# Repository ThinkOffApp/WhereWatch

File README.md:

# WhereWatch

**A pendant that remembers where you left things — fully local.** A tiny
wearable camera photo-logs your day into a Raspberry Pi at home; a local
vision model watches the trail. Ask *"where are my keys?"* and get back the
last photo that contains them, with a timestamp. No cloud, no subscription,
nothing leaves your house.

## Two devices. Zero cloud.

Plug in the Raspberry Pi. Charge the pendant over USB-C. Wear it.
That is the whole system. CodeWatch is the phone and watch dashboard for the same local *Watch family.

WhereWatch remembers where you placed your things, privately. The Pi stores
a photo of the last useful observation of an item, together with its time and
location. If people appear in a retained image, faces are blurred before that
image becomes part of the memory store.

- **No cloud service required**
- **No subscription required**
- **No video stored**
- **No face identification**
- **Faces blurred before retained images are written to storage**
- **Object-location history stays on the Pi in your home**

The product target is deliberately small: **pendant + Raspberry Pi**. A large
GPU box, desktop, NAS, M5 cluster, or hosted AI service may be useful for
experiments, but none is part of the required product architecture.

Sibling of [CarWatch](https://github.com/ThinkOffApp/CarWatch) (your car as a
team-chat agent), [ClawWatch](https://github.com/ThinkOffApp/ClawWatch)
(health on your wrist) and [CodeWatch](https://codewatch.app) (your agents on
your phone). This one watches where things went.

## Status — honesty first

**Design stage. Nothing here is built yet.** This README is the agreed
design; code lands as it is written and every feature will be labeled
*proven / built + tested / planned*, the same policy as CarWatch.

## The product principle

**Two objects, simple power.** The whole system is a pendant you wear and a Pi
box. The Pi stays plugged into power; the pendant charges over USB-C and runs
untethered. No monitor, no keyboard, no ethernet - the box joins wifi,
self-installs, self-updates (the CarWatch pattern), and everything you ever
touch is the pendant, the room agent, and the web page the box serves.

## The design

### Pendant (ESP32-S3 + OV5640 camera + 2Ah battery)

Hardware philosophy: minimal. **One button** (tap: voice tag, double-tap:
status check, hold: power), **one USB-C port** (charging, and wired transfer
as an offline option), a **tiny vibration motor** as the only output, no
screen, no LED. Covering the lens is the pause control.

Haptic status (double-tap the button): one buzz = on and connected, two
buzzes = on but offline, silence = off. The whole UI in your fingertips.

One device, two appetites, switching automatically by battery state:

| Mode | When | What | Battery |
|------|------|------|---------|
| Stream | charging or battery healthy | low-res MJPEG at 2 fps over wifi | ~5–8 h est. |
| Stills | below battery threshold | one photo every 20–30 s, deep sleep between | a full day+ |

Camera: **OV5640, 5 MP, wide-angle lens** — small objects need the pixels.
Dual-pipe capture: the 2 fps stream runs low-res (Frigate only needs motion),
while the frames that get indexed are full 5 MP stills, so "keys on a
cluttered table" survives with readable detail without spending battery on
5 MP video.

**Motion-gated transmission (battery multiplier):** the pendant only
transmits when something is actually happening. Two triggers, cheapest first:
on-device frame differencing (compare consecutive low-res frames, no extra
part needed) and optionally a tiny IMU (movement of the wearer). Still scene,
still wearer = radio off, deep sleep. Wifi transmit is the power hog, so
motion gating stretches every battery estimate above substantially.

### Base station (any Raspberry Pi–class box)

- **Cheap filter:** [Frigate](https://frigate.video) ingests the 2 fps
  stream and flags motion / person / object events — near-zero cost.
- **Expensive brain:** a local vision-language model (Qwen3.6-class with an
  mmproj projector, the same stack CarWatch runs) wakes only for flagged
  frames and all stills, captioning and inventorying each into a small index:
  *objects seen, where, when*.
- **The question:** "where are my keys" is a text search over the captions,
  answered with the newest matching photo and its timestamp — in your team
  chat, like every other agent in the family.

**Lens-cover pause:** covering the camera IS the pause button - a run of
all-dark frames stops capture and transmission until light returns. A
physical privacy gesture anyone in the room can see and perform, no app
needed.

**Voice tags ("leaving my keys here"):** the pendant carries a mic used ONLY
on explicit trigger - a button press or an on-device wake word (ESP32-S3
runs wake-word detection locally) - never ambient recording, the audio
equivalent of things-not-people. A short clip travels to the base station,
whisper transcribes it locally (the same stack the car uses), and the text
is pinned to that moment's photo and place in the index. Saying where you
put something beats hoping the camera noticed.

**Open decision (9 Oct 2026): ambient audio.** Audio-memory wearables record
conversations all day so you can ask about your day afterwards. WhereWatch
does not: an always-on mic records other people, which breaks
things-not-people and needs everyone's consent. This branch keeps the mic
trigger-only and builds the day recap from things only (plus the wearer's own
voice tags, once those exist).
Changing that is a product decision, not a setting.

### Interfaces (the family pattern: the agent is the front door)

- **Room agent:** WhereWatch joins your team rooms like its siblings - ask
  `@wherewatch where are my keys` from anywhere and it answers with the last
  matching photo and timestamp. Proactive too: it can post "keys last seen on
  the hallway table" when you leave home without them.
- **Watch app:** one screen, one question - speak or pick a recent object,
  get the photo on your wrist. The ClawWatch/CodeWatch wrist pattern.
- **Web app:** browse the captioned timeline, search history, manage
  retention and delete days - the place for anything bigger than a glance.

## The privacy line, drawn before the first commit

**Faces are blurred before storage.** Any face in a frame is scrubbed on the
Pi before the image touches disk - the stored history physically cannot
identify people. And **no video is ever stored**: the pendant's stream is
transient plumbing for motion detection; only stills survive.

**Things, not people - by design, in this branch.** WhereWatch indexes
OBJECTS only: the captioning prompt and the index schema have no notion of
who was in frame, person-class detections are dropped rather than stored,
and "where is Anna" is a question this system is built to be unable to
answer. That is a product decision, not a missing feature.

A wearable camera still photographs everyone around you, not just your keys.
WhereWatch is local-only by design — frames never leave your own hardware —
but that does not answer where wearing it is welcome. Decide that before
building the habit. The default firmware will ship with a physically obvious
lens (no hidden-camera styling) and a hardware off switch.

## Beyond "where are my keys" — same two boxes, more memory

The object-state memory answers more than lost-and-found, all local, no new
hardware:

- **Told, not seen:** say "leaving my keys here" (pendant button/wake word),
  type a note in the room chat ("note: passport is in the car"), or press the
  button - all three write the same observation record the camera would have.
  Your word outranks the camera's guess.
- **"Did I…?" checks:** did I lock the door, turn off the stove, take the
  medication, water the plants - the trail holds the last photo of the
  action, so the answer is a picture, not anxiety.
- **Running low:** the pantry/fridge shots know when the milk was last seen;
  a shopping hint falls out of the same index.
- **Before/after:** "what did the desk look like on Monday" - placement
  history doubles as a room diary.
- **Arrivals:** parcels, deliveries, things that appeared rather than moved.
- **Your day, recapped:** "what happened today" in a few sentences, written
  by the base station's local model from the day's sightings, with where each
  thing was last seen taken straight from the index (built in `base/`).
- **Tasks, told not seen (planned):** a voice tag like "remind me to call the
  bank" becomes a task note, and "what do I still need to do" lists the open
  ones. Same trigger-only mic, same note records.

Every one of these is a query over the SAME captioned-stills index; none
breaks the two-device boundary or the things-not-people rule.

## The emoji language

WhereWatch speaks in emoji - a friendly, wordless icon set that works on the
tiny display, in the app, and embossed on the case itself:

- **Objects:** 🔑 keys · 👛 wallet · 📱 phone · 🕶️ glasses · 🎧 headphones · 📕 docs · 🔋 battery
- **Location:** 📍 where it was last seen
- **Privacy promises, as a badge set:** 🎥🚫 no video · 🙈 no faces · ☁️🚫 no cloud

The privacy trio can be embossed right on the case as a wordless promise
anyone can read at a glance, and the same emoji tag each object in the app and
on the carried Badger. One little visual language across plastic, screen, and
software.

### Colorways + covers

Shell in **Black + four ThinkOff colors** (Fuchsia #D946EF, Orange #F97316,
Yellow #FACC15, Lime #84CC16), soft-touch finish. Your chosen color also
themes the web app accent.

Optional slip-on **covers** over the shell:
- **Soft silicone skin** - grippy, drop-protective, wipes clean.
- **Furry/plush cover** - the playful option. Cut-outs for the lens, button
  and USB-C. On-brand fun, and it makes the camera friendly and obviously a
  camera - the opposite of a hidden spy device, which fits the things-not-
  people ethos. Covers must never occlude the lens, mic port, or charge port.

## Hardware

The parts list, sourcing and pricing live in the team's private workspace,
not in this public repo.

Architecture and the strict pendant + Pi boundary: [ARCHITECTURE.md](ARCHITECTURE.md).

Future website/launch copy: [WEBSITE_COPY.md](WEBSITE_COPY.md).

## License

AGPL-3.0, like its siblings. Copyright (C) 2026 ThinkOff / Petrus Pennanen.

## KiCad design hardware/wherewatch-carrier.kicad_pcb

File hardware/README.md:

# WhereWatch carrier PCB (v0.3 schematic after two review passes, ERC clean; layout pending)

**Goal (petrus, 2026-09-09):** the pendant electronics on one board, assembled by JLCPCB, so no soldering is needed at home. Mic, speaker, 0.42" screen, 5 MP camera, GPS, motion, vibration, on an ESP32.

**Architecture:** a carrier board for the **Seeed XIAO ESP32S3 Sense**. JLCPCB places the XIAO module itself (their part C9900154951); the Sense expansion board with the OV5640 camera, the PDM microphone and the microSD slot clips on top as today. Everything else sits on the carrier as bare parts JLC also solders.

## Pin map (the carrier map; BUILD.md on main also carries the bench-build map with the purple face board, to be relabelled)

| XIAO pin | GPIO | carrier use |
|---|---|---|
| D0 | GPIO1 | battery divider midpoint (ADC), 100 k + 100 k + 100 nF |
| D1 | GPIO2 | button to GND (internal pull-up) |
| D2 | GPIO3 | GNSS ON/OFF (module pin 5, active-low shutdown), 100 k pulldown |
| D3 | GPIO4 | vibration motor driver IN |
| D4 | GPIO5 | I2C SDA: IMU + OLED |
| D5 | GPIO6 | I2C SCL: IMU + OLED |
| D6 | GPIO43 | UART TX → GNSS RX |
| D7 | GPIO44 | UART RX ← GNSS TX |
| D8 D9 D10 | GPIO7 8 9 | **I2S BCLK / LRCLK / DIN to the speaker amp** (decision 5 below): the XIAO ESP32S3's bottom pads carry only JTAG (used by the Sense board's mic and camera), USB, EN and the battery, so these three header pins are the only free GPIOs, and using them means **no microSD card in the pendant** |
| 3V3, GND, VBUS, B+, B− | — | rails; the cell reaches B+ through Q1; VBUS (USB present) only senses, via R2/R10 into Q2 |

## BOM v0 (JLCPCB part numbers verified 2026-09-09)

| # | function | part | JLC # | class |
|---|---|---|---|---|
| 1 | brain | Seeed XIAO ESP32S3 | C9900154951 | extended |
| 2 | motion | LSM6DS3TR-C, LGA-14 | C967633 | extended |
| 3 | GNSS | ATGM336H-5N31 | C90770 | extended |
| 4 | battery load switch | AO3401A P-MOSFET (Q1, 4 A) between the cell and the XIAO B+; gate 100 k up to the cell (off), pulled low by SW1 ("on") or by Q2 when USB is present | C15127 | basic |
| 5 | drivers (x2) | Q2 2N7002 (USB-present → Q1 on) C8545; Q3 AO3400A for the motor, RDS(on) specified at 2.5 V, 5.8 A | C8545 / C20917 | basic |
| 6 | flyback diode | 1N4148W | C81598 | basic |
| 7 | speaker amp | MAX98357A, TQFN-16, **VDD on VBAT after the switch** (review P0: +5V is USB-only) | C910544 | extended |
| 8 | screen | 0.42" 72x40 I2C OLED module | — | hand-fitted 4-pin header |
| 9, 12 | battery + speaker connectors | JST PH 2-pin S2B-PH-K-S | C173752 | extended |
| 10 | power switch | MSK-12C02, **as a gate control only** (rated 50 mA, codexmb second pass): common to GND, "on" throw grounds Q1's gate; off without USB = zero drain | C431540 | extended |
| 11 | button | TS-1187A-B-A-B | C318884 | basic |
| 13 | passives | 0402/0603 R, C | basic | basic |
| 14 | GNSS antenna connector | u.FL (J3), **as drawn on the board = option B (active, cabled patch)**; deleted only if Petrus picks option A | — | — |
| 15 | antenna bias | 47 nH from VCC_RF (L1), **as drawn on the board = option B**; deleted only if Petrus picks option A (passive: patch → RF_IN matching per the ATGM336H manual, no VCC_RF feed) | — | — |
| 16 | antenna | **OPEN, Petrus picks A or B (asked 2026-09-15):** A = PULSE W3225 passive ceramic patch, 25 mm, 4 mm high, 3 dBi, 50 Ω, SMD, machine-placed (rows 14/15 then go); B = active ceramic patch on a u.FL cable, hand-fitted, board as drawn | A: C7414031 (10 in stock 15.9., $4.89) | A: extended |
| 17 | pulldowns / gate resistors | 100 k on Q3 gate, 100 k on GNSS ON/OFF, 1 M Q1 gate pull-up (4 µA on), 10 k + 100 k on the VBUS sense, 100 k on the wake line | basic | basic |

## Open decisions (petrus / claudeMB)
1. GNSS antenna: **OPEN between A (placed passive W3225) and B (active, cabled).** 18:11Z "ceramic antenna sounds good", 18:20Z "we go with ready parts"; claudemm posed A/B afterwards and holds the layout change until Petrus answers. The board is drawn as B. (was: decided v0.2, review it:) active antenna path per the ATGM336H manual (VCC_RF → 47 nH → u.FL), so the carrier needs an active ceramic patch; the alternative is the manual's passive path with an AT2659 LNA stage (C92450) in front of RF_IN, chosen if an active patch does not fit the case.
2. Speaker: size and placement (15 mm 4 Ω candidate).
3. **DECIDED by Petrus 2026-09-15 18:11Z ("Yes can have the tiny oled and ceramic antenna sounds good"): OLED on the carrier.** BOM row 8 becomes a JLCPCB-placeable part (bare 0.42" 72x40 panel + FPC connector, or a module with a placeable header); claudemm picks the LCSC numbers, layout may start.
4. Outline: teardrop from `cad/pendant.scad`, 1.0 mm board.
5. **GNSS gating (decided in v0.1, review it):** the module's ON/OFF pin (active-low shutdown) is driven from D2 instead of an external high-side MOSFET switch, and VBAT stays on 3V3 (10 µA) so every wake is a hot start (≤1 s, not 35 s). The manual does not state the shutdown current; if the bench shows more than tens of µA, the AO3401A high-side switch comes back.
7. **Connectors: DECIDED by Petrus 2026-09-16 07:25Z ("SH").** J1, J4, J5 (battery, motor, speaker) change from JST PH S2B-PH-SM4 (5.5 mm tall) to JST SH side-entry SM02B-SRSS-TB (LCSC C160402, 2.9 mm tall, 1 A/pin, AWG 28–32); the stack under and over the board becomes 2.9 + 1.0 + 3.6 = 7.5 mm and fits the 8.2–8.5 mm cavity of case 1805429. Leads ordered pre-terminated (cell with SH pigtail or PH→SH adapter; motor and speaker with SH plugs). Footprint swap, re-route, DRC and re-export = claudeMB; the Seeed Fusion quote is re-run on the final BOM before ordering.
6. **Speaker vs microSD:** the I2S amp needs three GPIOs and the only free ones are D8–D10, which the Sense board's SD slot also uses. Proposal: no SD in the pendant (the base station stores everything), amp on D8–D10. Alternative: drop the speaker (the pendant vibrates and shows text; the base station speaks).

## Assembly plan v0.4: single-sided for JLCPCB Economic (2026-09-16, claudeMB)
JLCPCB's assembly capabilities page (read 2026-09-16): **Economic PCBA = single-sided placement only**, 2/4/6 layers,
single board from 10 x 10 mm, 2 to 50 pcs; **Standard PCBA does both sides but its single-board minimum is 70 x 70 mm**,
so this 37.5 x 26.1 mm board can only be machine-assembled as a one-sided Economic order. Layout v0.4 therefore puts
every JLC-placed part on the **bottom** (30 parts, 20 BOM lines, 12 Basic + 8 Extended) and leaves the **top** to the two
castellated modules that are hand-soldered at home, U1 (XIAO, JLC consign, no stock) and U3 (ATGM336H-5N31), plus J6.
- L1, Q3, D1 moved from the top to the bottom (`gen_pcb.py`: L1 placed beside J3, the packer is bottom-only).
- J6 is no longer the JST SH connector: four 1.0 mm solder pads on the top in the tip pocket (`lib/WhereWatch.pretty/
  OLED_Pads_1x04_P1.00mm`, courtyard = pads + 0.25 mm), DNP, hand-fitted only if a 0.42" OLED flex tail is ever wanted.
  The bottom had no room for the three moved parts with the SH connector there. Schematic still names the SH part; the
  footprint is what JLC sees. The case CAD's OLED window stays off.
- Routed with freerouting 1.9.0 (`logs/freerouting-single.log`, `out/route-single.ses`): all signal nets complete;
  `close_nets.py` is NOT needed for this route (it was for the v0.3 leftovers and shorts nets if run again).
- `stitch_gnd.py` now keeps vias out of footprint keepout areas (J3's u.FL top keepout).
- DRC (KiCad 10.0.6, errors): 0 violations, 0 unconnected. 328 tracks, 113 vias, 4 layers.
- Order files: `out/wherewatch-carrier-gerbers-single.zip` (15 Gerber/drill files), `out/wherewatch-carrier-bom-jlc.csv`
  (JLC-placed lines only), `out/wherewatch-carrier-cpl-jlc-bottom.csv` (30 bottom parts, JLC columns). Full BOM with
  tiers, stock and prices: `out/wherewatch-carrier-bom.csv`; full CPL: `out/wherewatch-carrier-cpl.csv`.
- Fee estimate from JLC's published table, five boards, not a quote: Economic setup 8.18 + stencil 1.53 + 8 Extended
  feeders 24.56 + 670 joints 11.79 + X-ray on the two leadless parts up to 16.40 + parts 20.71 = about USD 83, plus the
  bare PCB (7.10 parametric) and shipping, plus five XIAO and five ATGM336H bought separately.

## Verification before any order
Bench-prove the same circuit with the modules on jumper wires (ASSEMBLY.md) → KiCad ERC and DRC clean → JLCPCB DFM check on upload → second-agent review of the schematic against this pin map → first order 5 boards.

Room record: BOM v0 document `15fa6c35-3bc8-4eea-80b3-0ca6ff8ca643`, ideas line 9.

## Files
- `gen_schematic.py` → `wherewatch-carrier.kicad_sch` (regenerate after any edit; do not hand-edit the .kicad_sch). Connectivity is by global labels on pin ends.
- `sym-lib-table`, `fp-lib-table`, `wherewatch-carrier.kicad_pro`: project libraries (KiCad's bundled ones via `${KICAD10_SYMBOL_DIR}` / `${KICAD10_FOOTPRINT_DIR}`, plus `lib/`).
- `lib/`: vendored XIAO symbol + footprint (Seeed, CC BY-SA 4.0), the ATGM336H symbol, and footprints for the ATGM336H-5N31 and MSK-12C02 converted from the LCSC/EasyEDA records (see `lib/README.md`).
- `out/`: exported PDF/SVG/netlist of the current schematic.

## ERC status (KiCad 10.0.6, `kicad-cli sch erc --severity-all`)
0 errors. Accepted warnings: (1) `2N7002` and `1N4148W` are derived library symbols flattened by the generator, so ERC reports "doesn't match copy in library"; (2) LSM6DS3 SA0 tied to GND (address 0x6A) trips "bidirectional pin to power output" because GND carries a PWR_FLAG; (3) MAX98357A exposed pad to GND trips "unspecified pin to power input". None is a wiring fault.

## ATGM336H-5N31 pin table used (user manual §2.4)
1 GND · 2 TXD · 3 RXD · 4 1PPS · 5 ON/OFF (low = shutdown) · 6 VBAT · 7 NC · 8 VCC · 9 nRESET · 10 GND · 11 RF_IN · 12 GND · 13 NC · 14 VCC_RF · 15 reserved · 16 SDA · 17 SCL · 18 reserved. VCC 2.7–3.6 V, <25 mA running, 100 mA peak; UART default 9600.

## Review checklist before any order
- [ ] pin map above == BUILD.md == `gen_schematic.py` nets (second agent)
- [ ] footprint pad numbers for ATGM336H-5N31 and MSK-12C02 checked against the datasheets (converted from LCSC records; MSK-12C02: is pad 2 the common?)
- [ ] I2C addresses: LSM6DS3TR-C 0x6A, OLED 0x3C (no clash)
- [x] MAX98357A logic levels on a 4.2 V rail: VIH 1.3 V / VIL 0.6 V absolute (datasheet), 3.3 V I2S lines OK; SD_MODE = VDD selects the left word (firmware: mono on left)
- [x] ATGM336H active-antenna circuit needs no external DC block: the module provides antenna supply, detection and short protection internally (manual §2.7.1); only the 47 nH from VCC_RF
- [ ] I2S pins D8–D10 accepted (no microSD), decision 6
- [ ] GNSS ON/OFF gating accepted or MOSFET switch restored, decision 5
- [ ] ATGM336H nRESET left floating: manual says 不用时悬空 (leave floating when unused) — confirmed
- [ ] bench-proof on jumper wires done (ASSEMBLY.md)

## Review log
- 2026-09-09 19:06Z claudeMB (netlist read): P1 amp on USB-only +5V → **fixed** (VBAT); P2 Q3 gate floats at boot → **fixed** (R8 100 k); docs: README's "source of truth" wording vs BUILD.md's face-board table → wording fixed here, BUILD.md relabel awaits Petrus's OLED decision (bare 0.42" module on J6, purple board out).
- 2026-09-09 19:21Z codexmb full second report + claudeMB v0.3 read → **v0.3.1**: Q3 is AO3400A (RDS(on) specified at 2.5 V gate drive, 5.8 A; the 2N7002 was 115 mA and only specified at 5/10 V); IMU INT1 wired-OR onto the button line (BTN, D1) with an explicit 100 k pull-up, IMU set open-drain active-low in firmware, wake source read from WAKE_UP_SRC, so wrist-flick wake needs no extra XIAO pin; R1 1 M (4 µA while on); title block v0.3. AO3401A/AO3400A pin order 1 G, 2 S, 3 D confirmed in both the KiCad parents (TP0610T, Q_NMOS_GSD) and the AOS datasheets. Still open: no-cell USB behaviour (bench), motor stall current (needs the exact ERM part), PDF label overlap (cosmetic).
- 2026-09-09 19:16Z codexmb (second pass): MSK-12C02 is rated 12 V / 50 mA and sat in the battery path → **fixed v0.3**: it is a gate control for a 4 A P-MOSFET load switch, with a USB-present override so charging never passes through the switch; LSM6DS3 SDx/SCx must be VDDIO or GND in mode 1 → **fixed** (GND). MAX98357A VIH 1.3 V confirmed by codexmb from ADI too.
- 2026-09-09 19:07Z codexmb (independent): P0 same amp rail → fixed; P0 antenna path undocumented → **fixed** with the manual's active-antenna bias (L1 47 nH from VCC_RF); P1 ON/OFF pulldown → **fixed** (R9); P1 BUILD.md D8–D10 statement → docs, with the relabel; P1 MSK-12C02 pad 2 = common → still **[verify]** against the manufacturer drawing before layout; P1 GNSS shutdown current → bench measurement, on the checklist. Note from codexmb worth keeping: ERC cannot catch a rail that exists only on USB, because PWR_FLAG declares it powered; power-path review is a human/agent read of the netlist.

## Power budget (quiescent, carrier only)

| item | current | when |
|---|---|---|
| R1 gate pull-up (1 M from the cell) | ~4 µA | switch on |
| R6/R7 battery divider (200 k) | ~20 µA | switch on |
| R10 VBUS sense | 0 | no USB |
| GNSS off (ON/OFF low) | backup only, ~10 µA (datasheet, not total shutdown; bench) | switch on |
| everything | 0 (Q1 leakage) | switch off, no USB |

No-cell behaviour: with USB but no cell, the XIAO runs from VBUS, and VBAT carries whatever the onboard charger puts out with no battery attached; the amp and divider see that. Bring-up without a cell is fine for the S3, audio only with a cell. Bench check before fabrication (codexmb).

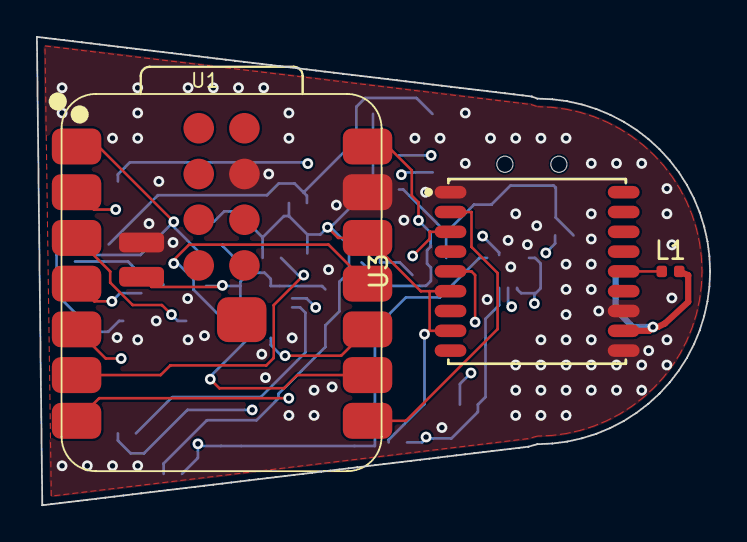
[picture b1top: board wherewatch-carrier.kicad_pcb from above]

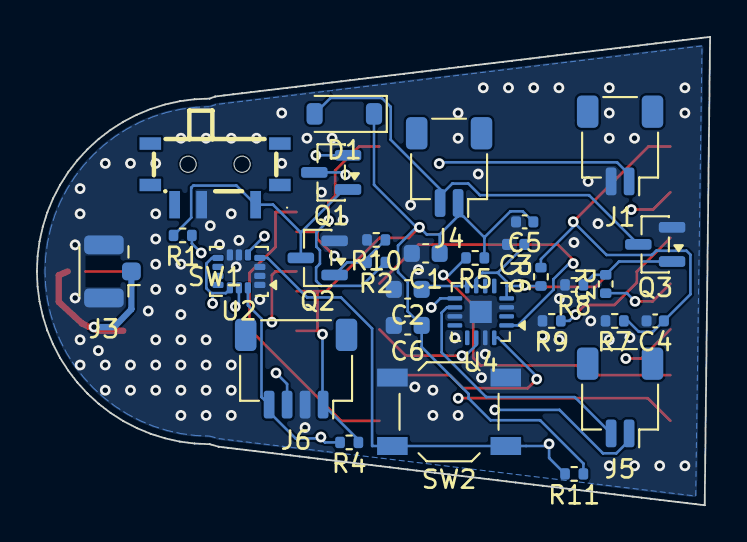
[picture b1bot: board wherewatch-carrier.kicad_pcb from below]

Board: 4 copper layers, 37.4 x 26.0 mm, 33 parts (30 on the bottom side), 24 nets.

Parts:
C1, C2, C6: C_0603_1608Metric
C3, C4, C5: C_0402_1005Metric
D1: D_SOD-123
J1, J4, J5: JST_SH_SM02B-SRSS-TB_1x02-1MP_P1.00mm_Horizontal
J3: U.FL_Hirose_U.FL-R-SMT-1_Vertical
J6: JST_SH_SM04B-SRSS-TB_1x04-1MP_P1.00mm_Horizontal
L1: L_0402_1005Metric
Q1, Q2, Q3: SOT-23
R1, R2, R3, R4, R5, R6, R7, R8, R9, R10, R11: R_0402_1005Metric
SW1: SW-TH_MSK12C02; MSK-12C02
SW2: SW_SPST_TL3342
U1: Val**; XIAO-ESP32-S3-SMD
U2: LGA-14_3x2.5mm_P0.5mm_LayoutBorder3x4y
U3: GPSM-SMD_ATGM336H-TR; ATGM336H-5N31
U4: TQFN-16-1EP_3x3mm_P0.5mm_EP1.23x1.23mm

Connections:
+3V3: C1.1, C5.1, C6.1, D1.1, J4.1, J6.1, R4.1, R5.1, R11.1, U1.12, U2.5, U2.8, U2.12, U3.6, U3.8
BAT_RAW: J1.1, Q1.2, R1.1
BTN: R11.2, SW2.1, U1.2, U2.4
GND: C1.2, C2.2, C3.2, C4.2, C5.2, C6.2, J1.2, J3.2, J6.2, Q2.2, Q3.2, R7.2, R8.2, R9.2, R10.2, SW1.2, SW2.2, U1.13, U1.18, U1.24, U2.1, U2.2, U2.3, U2.6, U2.7, U3.1, U3.10, U3.12, U4.3, U4.11, U4.15, U4.17
GNSS_EN: R9.1, U1.3, U3.5
GNSS_RF: J3.1, L1.2, U3.11
GNSS_RX: U1.7, U3.3
GNSS_TX: U1.8, U3.2
I2S_BCLK: U1.9, U4.16
I2S_DIN: U1.11, U4.1
I2S_LRCLK: U1.10, U4.14
SCL: J6.3, R5.2, U1.6, U2.13
SDA: J6.4, R4.2, U1.5, U2.14
SPK_N: J5.2, U4.10
SPK_P: J5.1, U4.9
SW_G: Q1.1, Q2.3, R1.2, SW1.1
VBAT: C2.1, C3.1, Q1.3, R6.1, U1.23, U4.4, U4.7, U4.8
VBAT_SENSE: C4.1, R6.2, R7.1, U1.1
VBUS: R2.1, U1.14
VBUS_DET: Q2.1, R2.2, R10.1
VCC_RF: L1.1, U3.14
VIB_IN: R3.1, U1.4
VIB_IN_R: Q3.1, R3.2, R8.1
VIB_N: D1.2, J4.2, Q3.3

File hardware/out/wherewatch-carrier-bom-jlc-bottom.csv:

Comment,Designator,Footprint,LCSC Part #
10u,"C1,C2,C6",C_0603_1608Metric,C19702
100n,"C3,C4,C5",C_0402_1005Metric,C1525
1N4148W,D1,D_SOD-123,C81598
LiPo JST PH,"J1,J4,J5",JST_SH_SM02B-SRSS-TB_1x02-1MP_P1.00mm_Horizontal,C160402
u.FL GNSS antenna,J3,U.FL_Hirose_U.FL-R-SMT-1_Vertical,C88374
OLED 0.42in I2C,J6,JST_SH_SM04B-SRSS-TB_1x04-1MP_P1.00mm_Horizontal,C160404
AO3401A,Q1,SOT-23,C15127
2N7002,Q2,SOT-23,C8545
AO3400A,Q3,SOT-23,C20917
1M,R1,R_0402_1005Metric,C26083
10k,R2,R_0402_1005Metric,C25744
1k,R3,R_0402_1005Metric,C11702
4.7k,"R4,R5",R_0402_1005Metric,C25900
100k,"R6,R7,R8,R9,R10,R11",R_0402_1005Metric,C25741
MSK-12C02,SW1,MSK-12C02,C431540
TS-1187A,SW2,SW_SPST_TL3342,C318884
LSM6DS3TR-C,U2,LGA-14_3x2.5mm_P0.5mm_LayoutBorder3x4y,C967633
MAX98357A,U4,TQFN-16-1EP_3x3mm_P0.5mm_EP1.23x1.23mm,C910544

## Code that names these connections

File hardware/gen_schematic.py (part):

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
# --- the brain: XIAO ESP32S3 (Sense board clips on top) --------------------
part('U1', 'Seeed_XIAO', 'XIAO-ESP32-S3-SMD', 'XIAO ESP32S3 Sense', fp='Seeed_XIAO:XIAO-ESP32-S3-SMD', at=(60, 70), nets={
    '1': 'VBAT_SENSE',   # D0 / GPIO1  battery divider midpoint (ADC)
    '2': 'BTN',          # D1 / GPIO2  button to GND
    '3': 'GNSS_EN',      # D2 / GPIO3  GNSS power enable
    '4': 'VIB_IN',       # D3 / GPIO4  vibration driver
    '5': 'SDA',          # D4 / GPIO5
    '6': 'SCL',          # D5 / GPIO6
    '7': 'GNSS_RX',      # D6 / GPIO43 XIAO TX -> GNSS RX
    '8': 'GNSS_TX',      # D7 / GPIO44 XIAO RX <- GNSS TX
    '9': 'I2S_BCLK',     # D8 / GPIO7  (decision 5: no microSD)
    '10': 'I2S_LRCLK',   # D9 / GPIO8
    '11': 'I2S_DIN',     # D10 / GPIO9
    '12': '+3V3',        # 3V3_OUT
    '13': 'GND',
    '18': 'GND',
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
